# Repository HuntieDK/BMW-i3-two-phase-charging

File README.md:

# BMW i3 60Ah two-phase charging

This repository contains schematics, PCB layout and Arduino IDE compatible
code for extending the BMW i3 60Ah BEV/REX charging to use two phases
for charging through the type 2 receptable in the car.

## Background

The BMW i3 60Ah is designed to charge with 230V/32A (7.4kW) from a single
phase supply. However often a three-phase 230V/16A supply is available
which can supply 11kW, but this only lets the i3 charge with 230V/16A (3.7kW),
as the i3 can only use one of the phases.

Internally in the car, the 32A current is split between two charging units,
the EME and the KLE. These actually pull up to 16A each, and can, with
modification, be made to charge from two individual phases. In this way,
the car can charge from two phases, 230V at 16A each, in total 7.4kW.

## Implementation

* The wiring in the car must be changed. A new three-phase socket must be
  installed and new wiring must be pulled from the replaced socket to the
  KLE and EME units

* The car must be persuaded to pull what it believes is 32A in order to
  pull 16A on each phase. That is accomplished by the electronics and
  firmware in this repository. It must be inserted in the proximity and
  control pilot signals between the car's charging socket and the charging
  controller, LIM. The main function of the circuit is to signal "32A" over
  the control pilot line whenever the connected EVSE signals "16A" or more.

## Warning

This modification of the BMW i3 60Ah IS NOT SIMPLE! It requires electrical,
mecanical and electronical skills to complete the modification succesfully
in a safe way. The information here is provided "as is" without warranty of
any kind. See attached license.

ANY WORK YOU PERFORM BASED ON THIS DESCRIPTION IS YOUR OWN RESPONSIBILITY!

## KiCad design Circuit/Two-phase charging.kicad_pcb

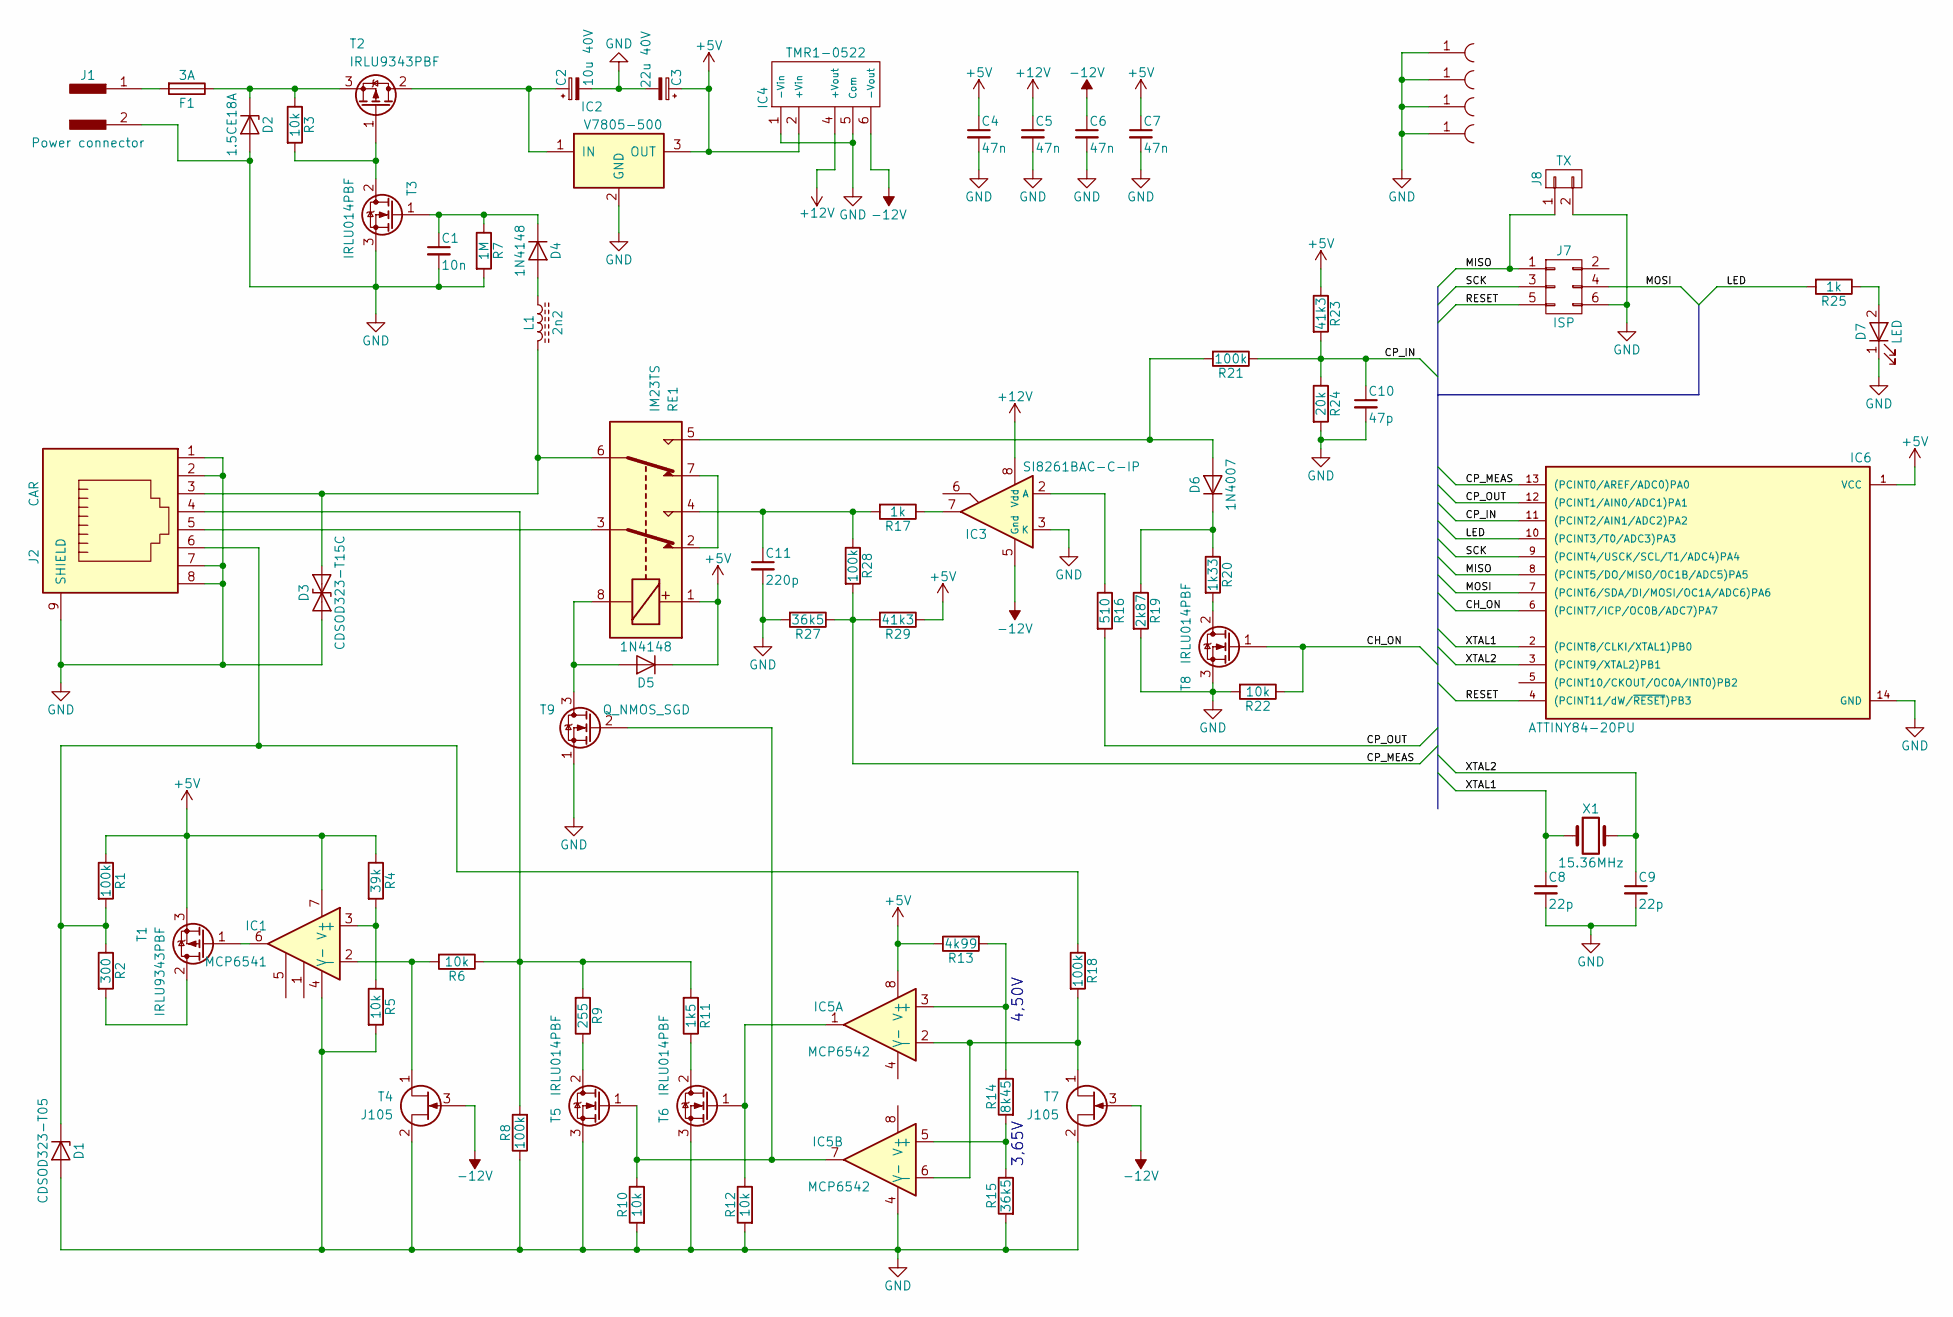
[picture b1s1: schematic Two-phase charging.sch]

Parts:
C1: 10n; C_Disc_D5.1mm_W3.2mm_P5.08mm
C2: 10u 40V; CP_Radial_D5.0mm_P2.50mm
C3: 22u 40V; CP_Radial_D5.0mm_P2.50mm
C4, C5, C6, C7: 47n; C_Disc_D5.1mm_W3.2mm_P5.08mm
C8, C9: 22p; Pin_Header_Straight_1x02_Pitch2.54mm
C10: 47p; Pin_Header_Straight_1x02_Pitch2.54mm
C11: 220p; Pin_Header_Straight_1x02_Pitch2.54mm
D1: CDSOD323-T05; D_SOD-323_HandSoldering
D2: 1.5CE18A; D_DO-201AD_P12.70mm_Horizontal
D3: CDSOD323-T15C; D_SOD-323_HandSoldering
D4, D5: 1N4148; D_DO-41_SOD81_P7.62mm_Horizontal
D6: 1N4007; D_DO-41_SOD81_P10.16mm_Horizontal
D7: LED; LED_D3.0mm
F1: 3A; R_Axial_DIN0207_L6.3mm_D2.5mm_P10.16mm_Horizontal
IC1: MCP6541; DIP-8_W7.62mm_LongPads
IC2: V7805-500; VX78xx-500
IC3: SI8261BAC-C-IP; DIP-8_W7.62mm_LongPads
IC4: TMR1-0522; Recom_1x05_Pitch2.54mm
IC5: MCP6542; DIP-8_W7.62mm_LongPads
IC6: ATTINY84-20PU; DIP-14_W7.62mm_LongPads
J1: Power connector; PINHEAD1-2
J2: CAR; RJ45_8_TM21R
J3, J4, J5, J6: Mount; MountingHole_3.5mm_Pad
J7: ISP; Pin_Header_Straight_2x03_Pitch2.54mm
J8: TX; Pin_Header_Straight_1x02_Pitch2.54mm
L1: 2n2; L_Axial_L11.0mm_D4.5mm_P5.08mm_Vertical_Fastron_MECC
R1, R8, R18, R21, R28: 100k; R_Axial_DIN0207_L6.3mm_D2.5mm_P10.16mm_Horizontal
R2: 300; R_Axial_DIN0207_L6.3mm_D2.5mm_P10.16mm_Horizontal
R3, R5, R6, R10, R12, R22: 10k; R_Axial_DIN0207_L6.3mm_D2.5mm_P10.16mm_Horizontal
R4: 39k; R_Axial_DIN0207_L6.3mm_D2.5mm_P10.16mm_Horizontal
R7: 1M; R_Axial_DIN0207_L6.3mm_D2.5mm_P10.16mm_Horizontal
R9: 255; R_Axial_DIN0207_L6.3mm_D2.5mm_P10.16mm_Horizontal
R11: 1k5; R_Axial_DIN0207_L6.3mm_D2.5mm_P10.16mm_Horizontal
R13: 4k99; R_Axial_DIN0207_L6.3mm_D2.5mm_P10.16mm_Horizontal
R14: 8k45; R_Axial_DIN0207_L6.3mm_D2.5mm_P10.16mm_Horizontal
R15, R27: 36k5; R_Axial_DIN0207_L6.3mm_D2.5mm_P10.16mm_Horizontal
R16: 510; R_Axial_DIN0207_L6.3mm_D2.5mm_P10.16mm_Horizontal
R17, R25: 1k; R_Axial_DIN0207_L6.3mm_D2.5mm_P10.16mm_Horizontal
R19: 2k87; R_Axial_DIN0207_L6.3mm_D2.5mm_P10.16mm_Horizontal
R20: 1k33; R_Axial_DIN0207_L6.3mm_D2.5mm_P10.16mm_Horizontal
R23, R29: 41k3; R_Axial_DIN0207_L6.3mm_D2.5mm_P10.16mm_Horizontal
R24: 20k; R_Axial_DIN0207_L6.3mm_D2.5mm_P10.16mm_Horizontal
RE1: IM23TS; Relay_DPDT_AXICOM_IMSeries_Pitch5.08mm
T1, T2: IRLU9343PBF; TO-251_IPAK_Vertical
T3, T5, T6, T8: IRLU014PBF; TO-251_IPAK_Vertical
T4, T7: J105; TO-92_Molded_Wide
T9: Q_NMOS_SGD; TO-92_Molded_Wide
X1: 15.36MHz; Crystal_HC49-U_Vertical

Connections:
+5V: C3.1, C4.1, C7.1, D5.1 (K), IC1.7 (V+), IC2.3 (OUT), IC4.2 (+Vin), IC5.8 (V+), IC6.1 (VCC), R1.1, R4.1, R13.1, R23.1, R29.1, RE1.1, T1.3 (S)
+12V: C5.1, IC3.8 (Vdd), IC4.4 (+Vout)
-12V: C6.1, IC3.5 (Gnd), IC4.6 (-Vout), T4.3 (G), T7.3 (G)
/CH_ON: IC6.6 ((PCINT7/ICP/OC0B/ADC7)PA7), R22.1, T8.1 (G)
/CP_IN: C10.1, IC6.11 ((PCINT2/AIN1/ADC2)PA2), R21.1, R23.2, R24.1
/CP_MEAS: IC6.13 ((PCINT0/AREF/ADC0)PA0), R27.1, R28.2, R29.2
/CP_OUT: IC6.12 ((PCINT1/AIN0/ADC1)PA1), R16.2
/LED: IC6.10 ((PCINT3/T0/ADC3)PA3), R25.2
/MISO: IC6.8 ((PCINT5/DO/MISO/OC1B/ADC5)PA5), J7.1, J8.1
/MOSI: IC6.7 ((PCINT6/SDA/DI/MOSI/OC1A/ADC6)PA6), J7.4
/RESET: IC6.4 ((PCINT11/dW/~RESET~)PB3), J7.5
/SCK: IC6.9 ((PCINT4/USCK/SCL/T1/ADC4)PA4), J7.3
/XTAL1: C8.1, IC6.2 ((PCINT8/CLKI/XTAL1)PB0), X1.1
/XTAL2: C9.1, IC6.3 ((PCINT9/XTAL2)PB1), X1.2
GND: C1.2, C2.2, C3.2, C4.2, C5.2, C6.2, C7.2, C8.2, C9.2, C10.2, C11.2, D1.2 (A), D2.2 (A), D3.1 (A1), D7.1 (K), IC1.4 (V-), IC2.2 (GND), IC3.3 (K), IC4.1 (-Vin), IC4.5 (Com), IC5.4 (V-), IC6.14 (GND), J1.2, J2.1, J2.2, J2.7, J2.8, J2.9 (SHIELD), J3.1, J4.1, J5.1, J6.1, J7.6, J8.2, R5.2, R7.2, R8.1, R10.2, R12.2, R15.2, R19.2, R22.2, R24.2, R27.2, T3.3 (S), T4.2 (S), T5.3 (S), T6.3 (S), T7.2 (S), T8.3 (S), T9.1 (S)
unnamed: C1.1, D4.1 (K), R7.1, T3.1 (G)
unnamed: C2.1, IC2.1 (IN), T2.2 (D)
unnamed: C11.1, R17.2, R28.1, RE1.4
unnamed: D1.1 (K), J2.6, R1.2, R2.1, R18.1
unnamed: D2.1 (K), F1.1, R3.1, T2.3 (S)
unnamed: D3.2 (A2), J2.3, L1.2, RE1.6
unnamed: D4.2 (A), L1.1
unnamed: D5.2 (A), RE1.8, T9.3 (D)
unnamed: D6.1 (K), R19.1, R20.1
unnamed: D6.2 (A), R21.2, RE1.5
unnamed: D7.2 (A), R25.1
unnamed: F1.2, J1.1
unnamed: IC1.2 (-), R6.2, T4.1 (D)
unnamed: IC1.3 (+), R4.2, R5.1
unnamed: IC1.6, T1.1 (G)
unnamed: IC3.2 (A), R16.1
unnamed: IC3.7, R17.1
unnamed: IC5.1, R12.1, T6.1 (G)
unnamed: IC5.2 (-), IC5.6 (-), R18.2, T7.1 (D)
unnamed: IC5.3 (+), R13.2, R14.1
unnamed: IC5.5 (+), R14.2, R15.1
unnamed: IC5.7, R10.1, T5.1 (G), T9.2 (G)
unnamed: J2.4, R6.1, R8.2, R9.2, R11.2
unnamed: J2.5, RE1.3
unnamed: R2.2, T1.2 (D)
unnamed: R3.2, T2.1 (G), T3.2 (D)
unnamed: R9.1, T5.2 (D)
unnamed: R11.1, T6.2 (D)
unnamed: R20.2, T8.2 (D)
unnamed: RE1.2, RE1.7

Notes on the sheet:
3,65V
4,50V

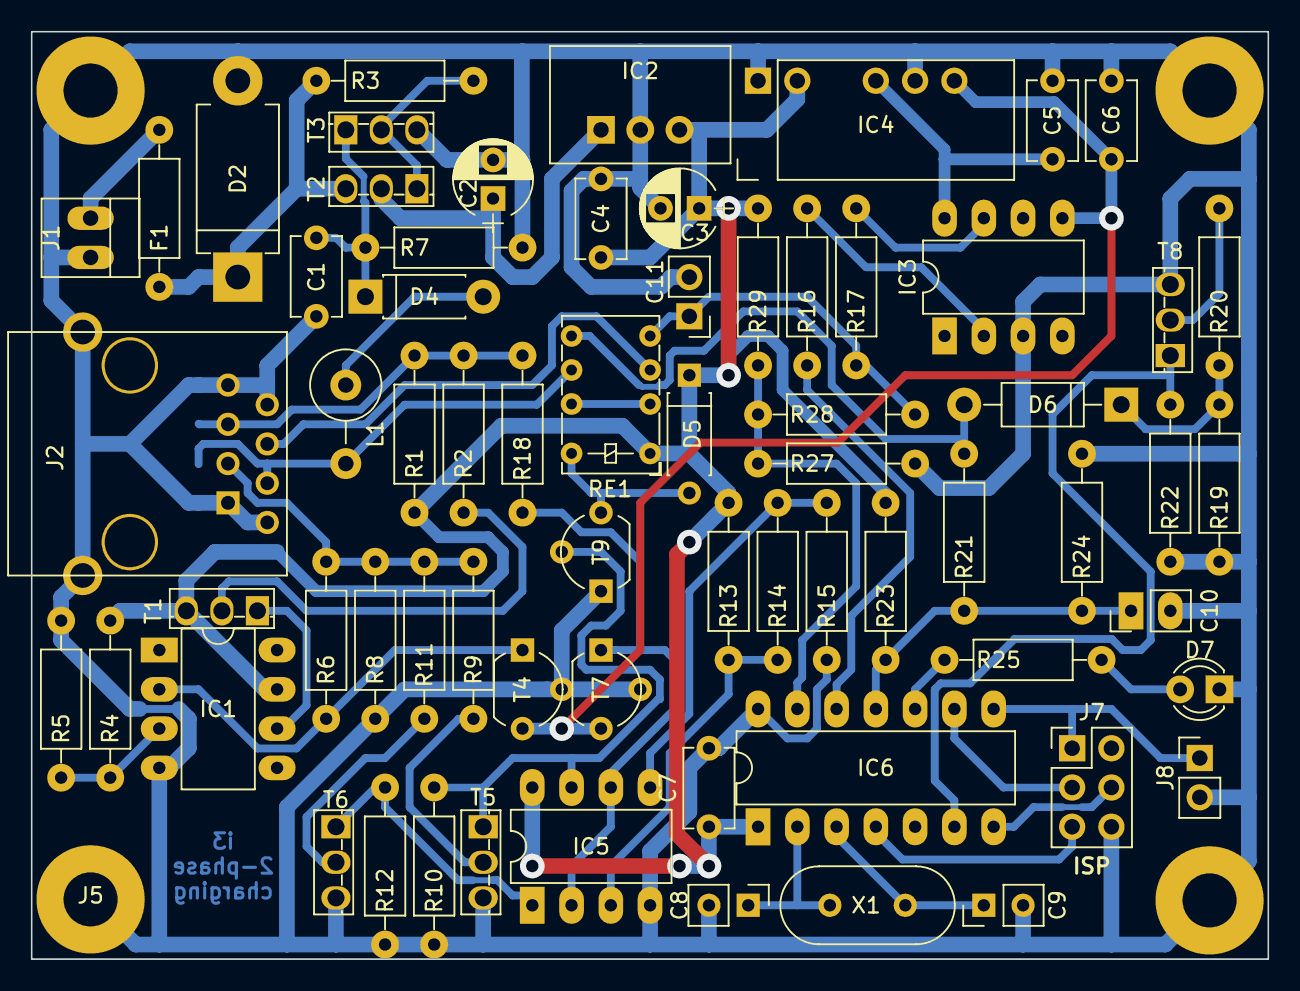
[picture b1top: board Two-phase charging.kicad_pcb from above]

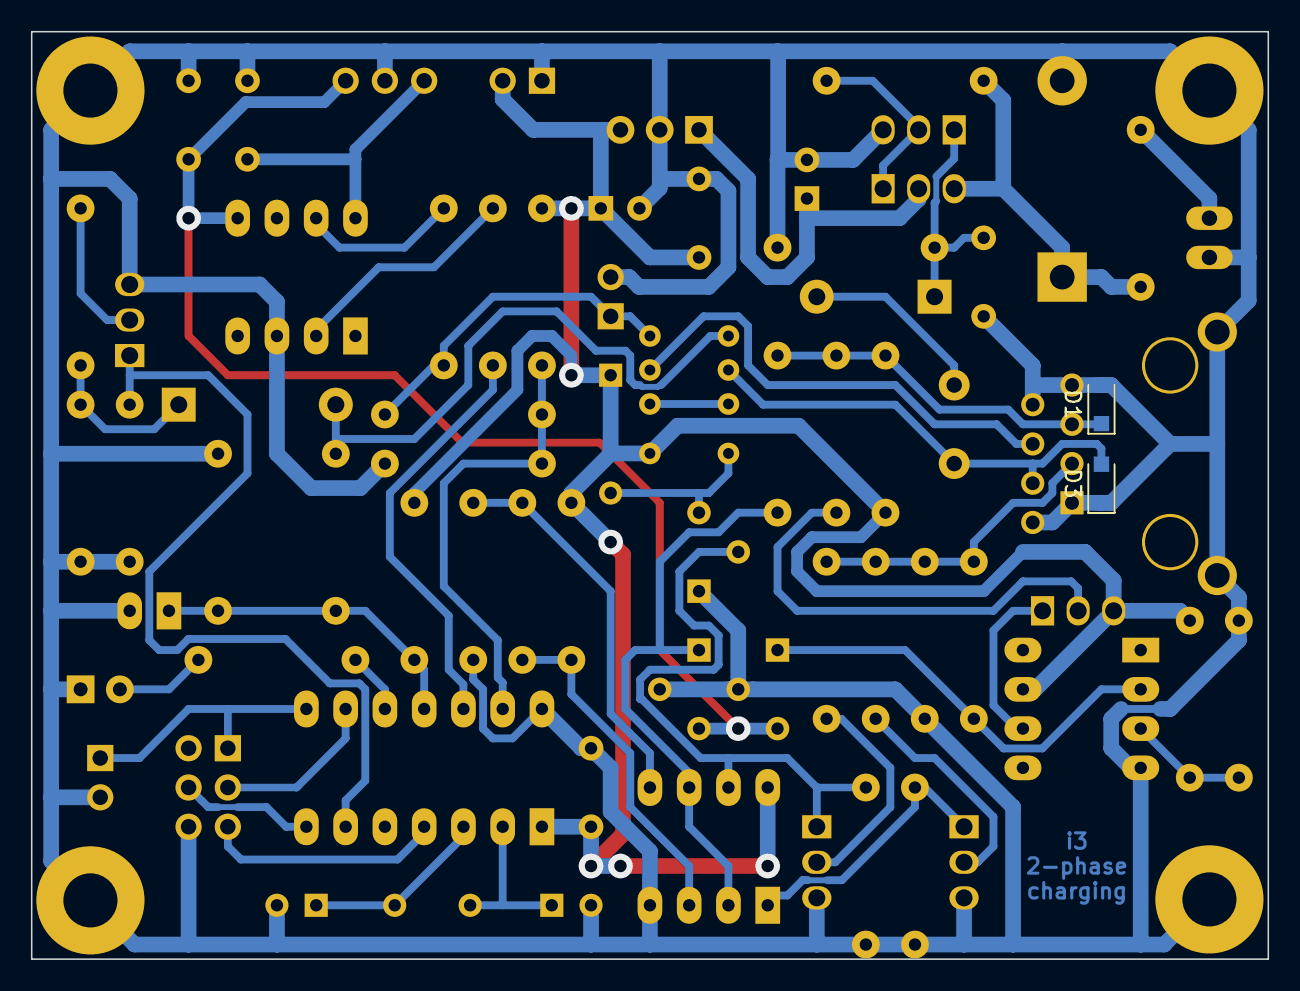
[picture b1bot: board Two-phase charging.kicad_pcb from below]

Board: 2 copper layers, 80.0 x 60.0 mm, 73 parts (2 on the bottom side), 45 nets.

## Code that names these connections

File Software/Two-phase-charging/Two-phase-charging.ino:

// Sketch for Attiny84 handling two-phase charging extension in BMW i3

#include "USISerialSend.h"

#define PIN_CP_MEAS 0   // PA0 pin 13
#define PIN_CP_OUT  1   // PA2 pin 12
#define PIN_CP_IN   2   // PA2 pin 11
#define PIN_LED_OUT 3   // PA3 pin 10
#define PIN_CH_ON   7   // PA7 pin 6

#define AD_CP_MEAS  0   // ADC port to read CP voltage
#define AD_CP_IN    2   // ADC port to detect ingoing CP

// Our clock frequency is 15.36 MHz. 6A = 10% pwm so 1A = 10/6% of 10 us = 16 2/3 us.
// Our clock tick is 1/15.36 us, so clocks/amp = 16 2/3*15.36 = 256.

#define AMPCNT(current) (static_cast<unsigned int>(current) << 8)  // Multiply by 256
#define AMPCNT_HALF     (128)

#define MEASCNT         AMPCNT(3)     // Measurement at 5% of cycle after each change
#define EXTENDCNT       (AMPCNT(15))  // If 16A (actually >= 15.5A) indicated, double current.

#define WR_HL_WRAP(REGH, REGL, VAL) { REGH = ((VAL)>>8)&0xff; REGL = (VAL)&0xff; }
#define WR_HL(REG, VAL) WR_HL_WRAP(REG##H, REG##L, VAL)

#define RD_LH_WRAP(REGH, REGL, VAL) { register byte reg = REGL; VAL = (static_cast<word>(REGH) << 8) | reg; }
#define RD_LH(REG, VAL) RD_LH_WRAP(REG##H, REG##L, VAL)

#define STOP_TIMER    { TCCR1B = 0; }         // Counter stopped
#define START_TIMER   { STOP_TIMER; WR_HL(TCNT1, 0); TCCR1B = _BV(CS10); } // No prescaling i.e. 15.36MHz counting.

#define LEVEL_UNDEF     0
#define LEVEL_LOW12     1
#define LEVEL_HIGH3     2
#define LEVEL_HIGH6     3
#define LEVEL_HIGH9     4
#define LEVEL_HIGH12    5
#define N_LEVELS        6

static const byte levelMap[1023*3/100] /*PROGMEM*/ = {
  LEVEL_LOW12,  // -12 - -11
  LEVEL_UNDEF,  // -11 - -10
  LEVEL_UNDEF,  // -10 - -9
  LEVEL_UNDEF,  // -9  - -8
  LEVEL_UNDEF,  // -8  - -7
  LEVEL_UNDEF,  // -7  - -6
  LEVEL_UNDEF,  // -6  - -5
  LEVEL_UNDEF,  // -5  - -4
  LEVEL_UNDEF,  // -4  - -3
  LEVEL_UNDEF,  // -3  - -2
  LEVEL_UNDEF,  // -2  - -1
  LEVEL_UNDEF,  // -1  -  0
  LEVEL_UNDEF,  //  0  -  1
  LEVEL_UNDEF,  //  1  -  2
  LEVEL_HIGH3,  //  2  -  3
  LEVEL_HIGH3,  //  3  -  4
  LEVEL_UNDEF,  //  4  -  5
  LEVEL_HIGH6,  //  5  -  6
  LEVEL_HIGH6,  //  6  -  7
  LEVEL_UNDEF,  //  7  -  8
  LEVEL_HIGH9,  //  8  -  9
  LEVEL_HIGH9,  //  9  - 10
  LEVEL_UNDEF,  // 10  - 11
  LEVEL_HIGH12, // 11  - 12
  LEVEL_HIGH12, // 12  - 13
  LEVEL_UNDEF,  // 13  - 14
  LEVEL_UNDEF,  // 14  - 15
  LEVEL_UNDEF,  // 15  - 16
  LEVEL_UNDEF,  // 16  - 17
  LEVEL_UNDEF,  // 17  - 18
};

static bool cpIn = false; // Indicate last CP input (true = high)

static word upCnt = 0;  // Number of rising CP edges
static word dnCnt = 0;  // Number of falling CP edges

static bool extending = false;  // Currently extending PWM
static byte evseCurrent = 0;  // Number of ampere indicated by EVSE

static bool doing32A = false;  // True when extending to 32A

void setup() {
  // put your setup code here, to run once:

  // Init status led:
  pinMode(PIN_LED_OUT, OUTPUT);  // Status LED
  digitalWrite(PIN_LED_OUT, LOW);

  // Init other pins:
  pinMode(PIN_CP_OUT, OUTPUT);     // PWM output initially high
  digitalWrite(PIN_CP_OUT, HIGH);

  pinMode(PIN_CH_ON, OUTPUT);       // Charge indication to car initially off
  digitalWrite(PIN_CH_ON, LOW);
  
  word pilot = 0;
  
  analogReference(DEFAULT);       // 5V analog reference
  
  // Set up AD manually for car CP measurements as it must be interrupt controlled:
  ADCSRA = _BV(ADEN)|_BV(ADIE)|_BV(ADPS2);  // Enable ADC, ADC interrupts, clock divisor 16
  ADCSRB = 0;
  ADMUX = AD_CP_MEAS;
  DIDR0 |= _BV(AD_CP_MEAS);  // Disable digital input on A0

  // Set up timer 1 for duty-cycle measurement and AD start interrupt
  TCCR1A  = 0;
  TCCR1B  = 0; // Prescaler disabled so timer is stopped
  TCCR1C  = 0;
  TIMSK1  = _BV(OCIE1A)|_BV(OCIE1B)|_BV(TOIE1);  // Interrupt on match OCR1A: 5% passed; measure CP voltage; interrupt on match OCR1B: Max PWM reached and on full run (line stuck)
  TIFR1   = 0;
  WR_HL(OCR1A, MEASCNT);      // First interrupt at measurement PWM
  WR_HL(OCR1B, EXTENDCNT);    // Second interrupt at PWM wide enough for us to expand to 32A
  WR_HL(ICR1, 0);
  WR_HL(TCNT1, 0);  // Initialize timer value

  // Initialize comparator
  ADCSRB  &=  ~_BV(ACME);           // Clear ACME flag to prepare for bandgap as reference
  ACSR    =   _BV(ACBG)|_BV(ACIE);  // (Enable), use bandgap, enable interrupts, (interrupt on toggle)
  DIDR0   |= _BV(AD_CP_IN);  // Disable digital input on A0

  // We're running; most stuff will run in interrupt routines.
  serialSetup();
  serialWrite("BMW i3 two phase charging running\n\r");
}

ISR(ANA_COMP_vect)  // Control pilot toggled.
{
  cpIn = (ACSR & _BV(ACO)) == 0;    // Current CP state from EVSE

  if (cpIn) {
    digitalWrite(PIN_CP_OUT, HIGH); // Output CP high
    upCnt++;  // We got a leading CP edge.
    WR_HL(OCR1B, EXTENDCNT);   // Interrupt at time ready for extending to 32A
    extending = false;  // not yet extending
    START_TIMER;  // Start the timer so we will make the relevant measurements.*/
  } else {
    if (!extending) {
      digitalWrite(PIN_CP_OUT, LOW); // Output CP low as we're not extending to 32A at the moment.
    }
    dnCnt++;
    // Read timer value to get high PWM %
    register word cnt;
    RD_LH(TCNT1, cnt);
    evseCurrent = (cnt+AMPCNT_HALF) >> 8;
    doing32A = cnt >= EXTENDCNT;
    if (!extending) {
      START_TIMER;  // Start timer for negative cycle measurement
    } // Else: Wait for extending done
  }
}

ISR(TIMER1_COMPA_vect)  // Timer compare interrupt - start AD
{
  ADCSRA |= _BV(ADSC); // Start conversion
  if (!cpIn) {
    STOP_TIMER;  // No need for timer interrupts during negative cycle
  }
}

ISR(TIMER1_COMPB_vect)  // Timer reached 15.5A or 32A marks
{
  if (!extending) {
    if (cpIn) {
      // CP signal is still active - extend to 32A
      WR_HL(OCR1B, AMPCNT(32));  // Call this routine again at 32A mark
      extending = true;
    } else {
      // CP signal not active any more - stop timer. Actually we should never get here as timer is reset at AD point in negative cycle.
      STOP_TIMER;
    }
  } else {
    // We are extending and reached 32A mark - stop extending and stop timer
    digitalWrite(PIN_CP_OUT, LOW);  // Stop overriding PWM
    extending = false;
    START_TIMER;  // Start timer for negative cycle measurement
  }
}

// CP measurement:
static byte portLevel[2] = { LEVEL_HIGH12, LEVEL_HIGH12 };
static volatile bool chargeOn = false;

static uint16_t measureLevel[2] = {0,0};

ISR(ADC_vect)
{
  uint16_t level;
  RD_LH(ADC, level);
  sei();
  measureLevel[cpIn] = level;
  portLevel[cpIn] = levelMap[level * 3 / 100];
  
  chargeOn = portLevel[false] == LEVEL_LOW12 && (portLevel[true] == LEVEL_HIGH6 || portLevel[true] == LEVEL_HIGH3);
  digitalWrite(PIN_CH_ON, chargeOn ? HIGH : LOW);
}

// No need for timer overflow for now: ISR(TIMER1_OVF_vect)  {}

static bool prevChargeOn = false;
static bool prev32A = false;
static bool prevDC = false;
static byte prevCurrent = 0;

char s[16];

static const char* on = "ON\r\n";
static const char* off = "OFF\r\n";

void loop()
{
  bool dc = (evseCurrent >= 2 && evseCurrent <= 4);
  register byte act = chargeOn ? LOW : HIGH;
  register byte inAct = chargeOn ? HIGH : LOW;
  digitalWrite(PIN_LED_OUT, inAct);
  serialDelay(1200);
  digitalWrite(PIN_LED_OUT, (doing32A) ? act : inAct);
  serialDelay(200);
  digitalWrite(PIN_LED_OUT, inAct);
  serialDelay(200);
  digitalWrite(PIN_LED_OUT, act);
  serialDelay(200);

  if (chargeOn != prevChargeOn) {
    serialWrite("Charging: ");
    serialWrite(chargeOn ? on : off);
    prevChargeOn = chargeOn;
  }

  if (doing32A != prev32A) {
    serialWrite("32A extending: ");
    serialWrite(doing32A ? on : off);
    prev32A = doing32A;
  }

  if (prevDC != dc) {
    serialWrite("DC charger: ");
    serialWrite(dc ? on : off);
    prevDC = dc;
  }

  if (prevCurrent != evseCurrent) {
    serialWrite("EVSE current: ");
    sprintf(s, "%d", evseCurrent);
    serialWrite(s);
    serialWrite("\r\n");
    prevCurrent = evseCurrent;
  }
  
  /*serialWrite("Upcount: ");
  sprintf(s, "%d\r\n", upCnt);
  serialWrite(s);
  serialWrite("Downcount: ");
  sprintf(s, "%d\r\n", dnCnt);
  serialWrite(s);

  serialWrite("Level[0]: ");
  sprintf(s, "%d\r\n", portLevel[false]);
  serialWrite(s);
  serialWrite("Level[1]: ");
  sprintf(s, "%d\r\n", portLevel[true]);
  serialWrite(s);*/
}

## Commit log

2017-08-23 Added schematics and PCB layout
2017-08-23 Added schematics and PCB
2017-08-23 Added arduino source for ATTINY84
2017-09-01 Added license
2017-09-01 More description
2017-09-16 Fixed library path level
2017-11-17 Added schematics as PDF
2019-03-31 Some PCB layout improvements
